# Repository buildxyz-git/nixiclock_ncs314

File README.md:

# BuildXYZ firmware for the NCS314 NixieClock from GRA&AFCH.

Updates include:
- General code refactoring
- Move most configuration parameters to NixieConfig.h
- Remove IR Remote functionality
- Enable/Disable GPS in config file
- Enable/Disable Debugging in config file
- Added more tunes in config file
- Tube timer feature with on/off timer to turn tube off at night
- Temperature LED feature to reflect room temperature in LED color
- Enable/Disable Colons in config file
- Remove IR functionality
- Remove hours offset in menu
- Bugfix: Timer3 interrupt being used by tone library not allowing red LED PWM on D9, opt for block tone library 

# Installation
clone this repo!
`git clone https://github.com/buildxyz-git/nixiclock_ncs314.git`

Install a few libraries:
[TimeZone](https://github.com/JChristensen/Timezone)
[TimerFreeTone](https://bitbucket.org/teckel12/arduino-timer-free-tone/downloads/)

Copy the patched version of RTTTL included in this repo
`NixieClock_NCS314_Firmware> cp -r ./libs/Rtttl [/PATH/TO/YOUR/ARDUINO/LIBRARIES]`

Open the main sketch (NixieClock_NCS314_Firmware.ino) and build!

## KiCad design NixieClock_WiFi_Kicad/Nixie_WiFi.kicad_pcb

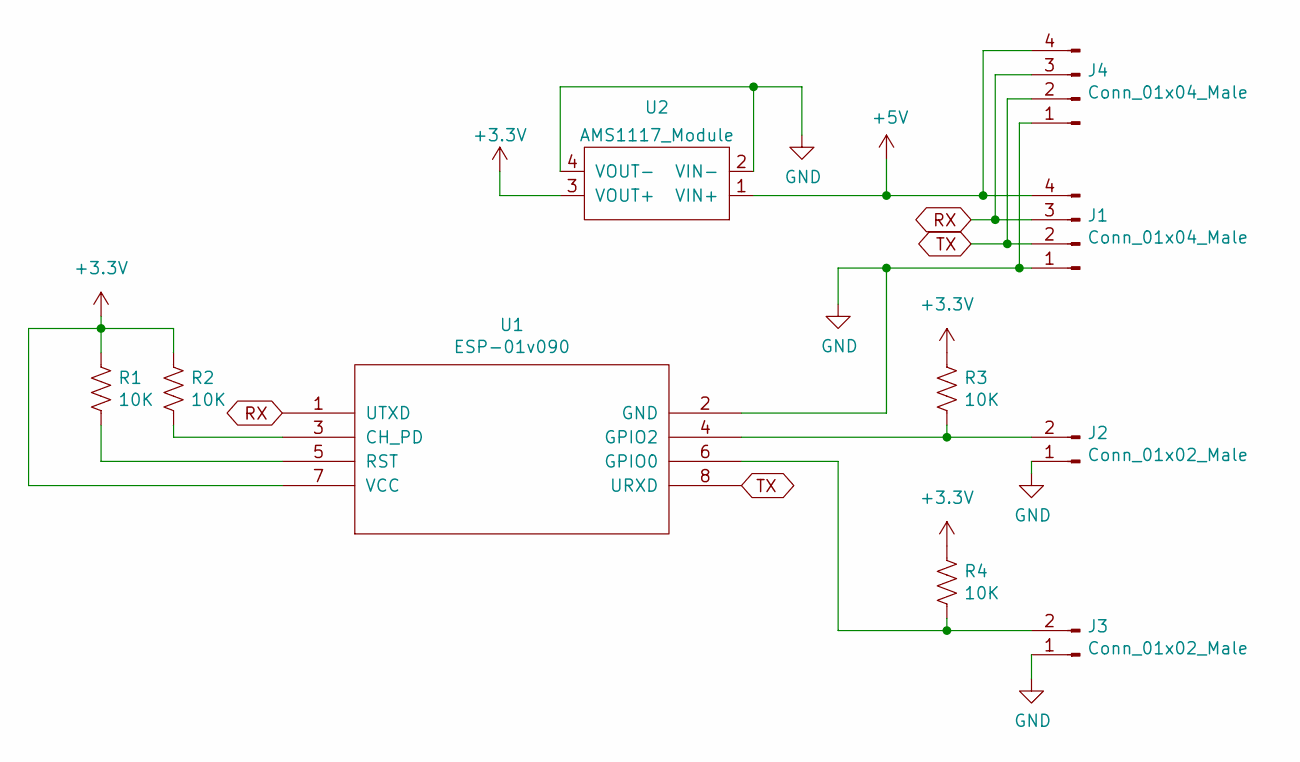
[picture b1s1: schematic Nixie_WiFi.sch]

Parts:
J1, J4: Conn_01x04_Male; PinHeader_1x04_P2.54mm_Vertical
J2, J3: Conn_01x02_Male; PinHeader_1x02_P2.54mm_Vertical
R1, R2, R3, R4: 10K; R_Axial_DIN0207_L6.3mm_D2.5mm_P10.16mm_Horizontal
U1: ESP-01v090; ESP-01
U2: AMS1117_Module

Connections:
+3V3: R1.1, R2.1, R3.1, R4.1, U1.7 (VCC), U2.3 (VOUT+)
+5V: J1.4, J4.4, U2.1 (VIN+)
GND: J1.1, J2.1, J3.1, J4.1, U1.2 (GND), U2.2 (VIN-), U2.4 (VOUT-)
unnamed: J2.2, R3.2, U1.4 (GPIO2)
unnamed: J3.2, R4.2, U1.6 (GPIO0)
unnamed: R1.2, U1.5 (RST)
unnamed: R2.2, U1.3 (CH_PD)
RX: J1.3, J4.3, U1.1 (UTXD)
TX: J1.2, J4.2, U1.8 (URXD)

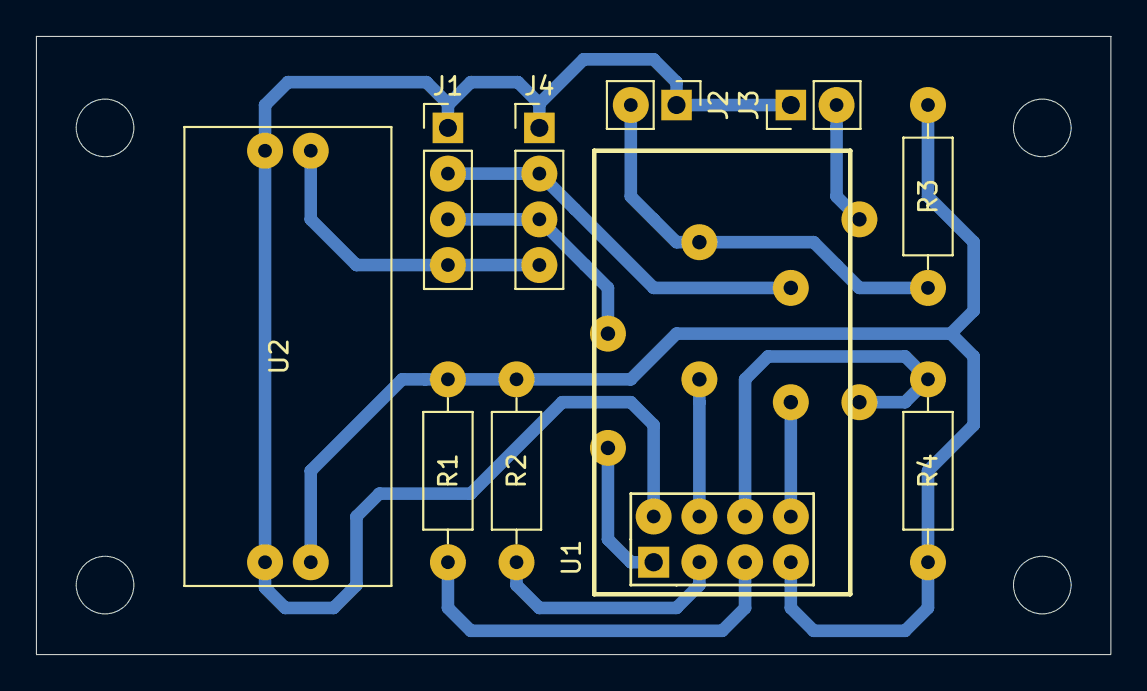
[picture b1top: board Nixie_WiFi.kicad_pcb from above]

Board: 2 copper layers, 59.7 x 34.3 mm, 10 parts (0 on the bottom side), 9 nets.

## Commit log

2020-03-17 Add RTTTL library dependency, update READAME
2020-08-20 added compiled .hex image and additional supporting libraries
